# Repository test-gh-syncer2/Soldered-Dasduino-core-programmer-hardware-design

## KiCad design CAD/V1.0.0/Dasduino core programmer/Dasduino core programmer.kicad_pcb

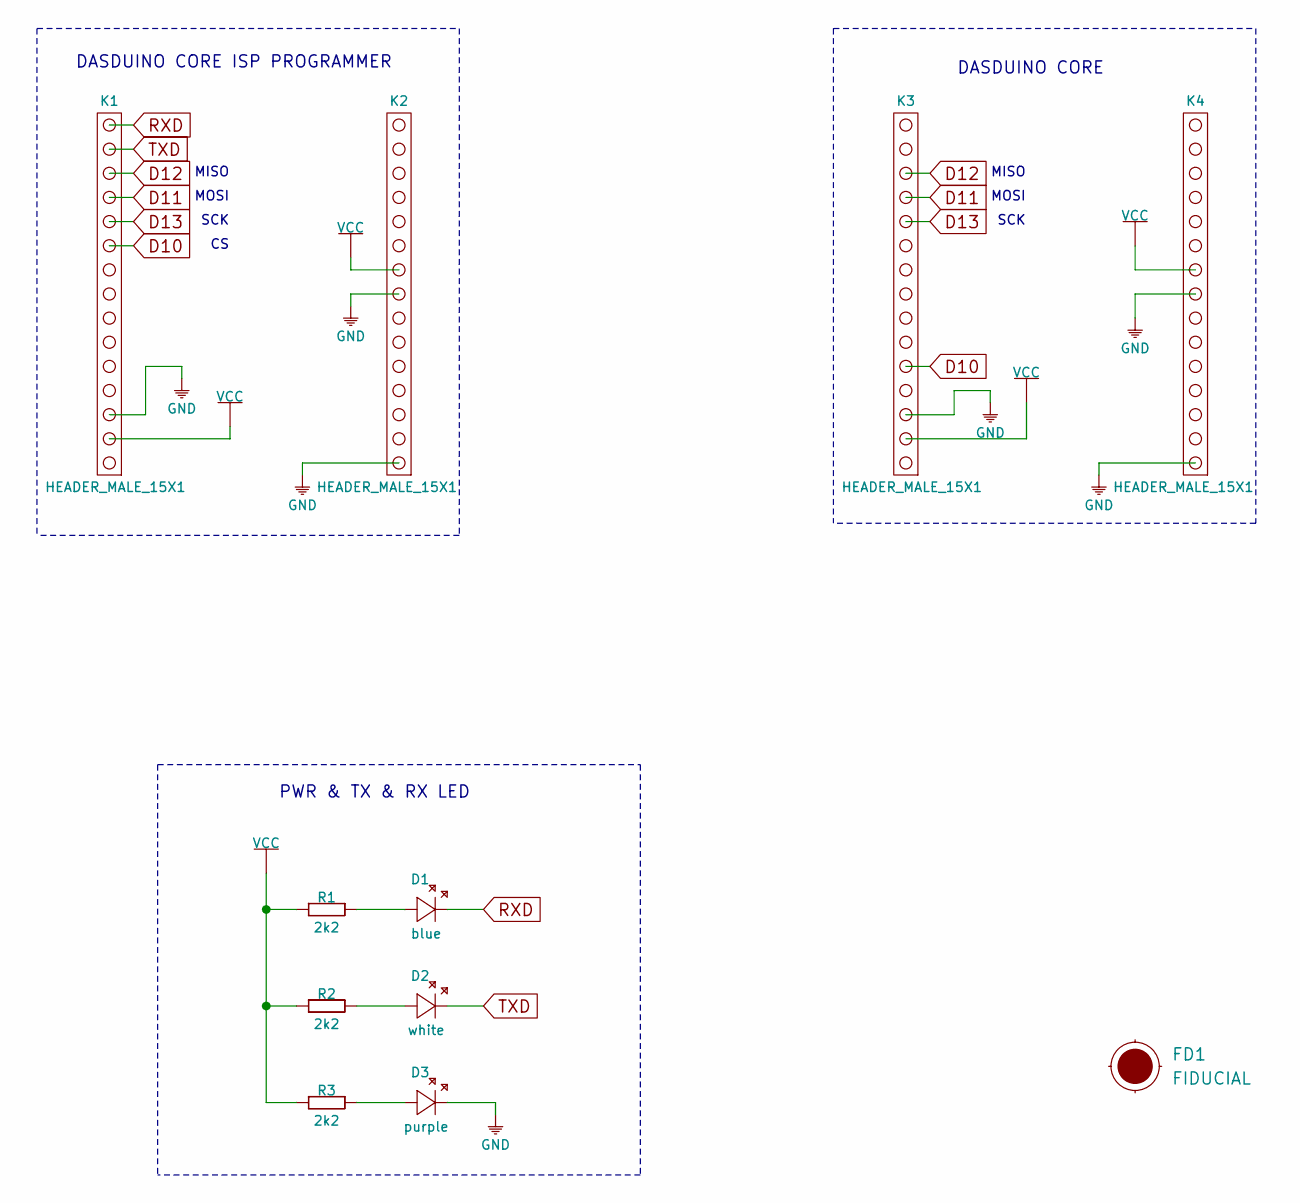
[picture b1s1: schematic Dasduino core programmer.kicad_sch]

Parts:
D1: blue; 0402LED
D2: white; 0402LED
D3: purple; 0402LED
FD1: FIDUCIAL; FIDUCIAL_23
K1, K2, K3, K4: HEADER_MALE_15X1
R1, R2, R3: 2k2; 0402R

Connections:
D10: K1.10, K3.5
D11: K1.12, K3.12
D12: K1.13, K3.13
D13: K1.11, K3.11
GND: D3.2 (K), K1.3, K2.1, K2.8, K3.3, K4.1, K4.8
unnamed: D1.1 (A), R1.2
unnamed: D2.1 (A), R2.2
unnamed: D3.1 (A), R3.2
RXD: D1.2 (K), K1.15
TXD: D2.2 (K), K1.14
VCC: K1.2, K2.9, K3.2, K4.9, R1.1, R2.1, R3.1

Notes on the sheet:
MISO
MOSI
SCK
PWR & TX & RX LED
DASDUINO CORE ISP PROGRAMMER
DASDUINO CORE

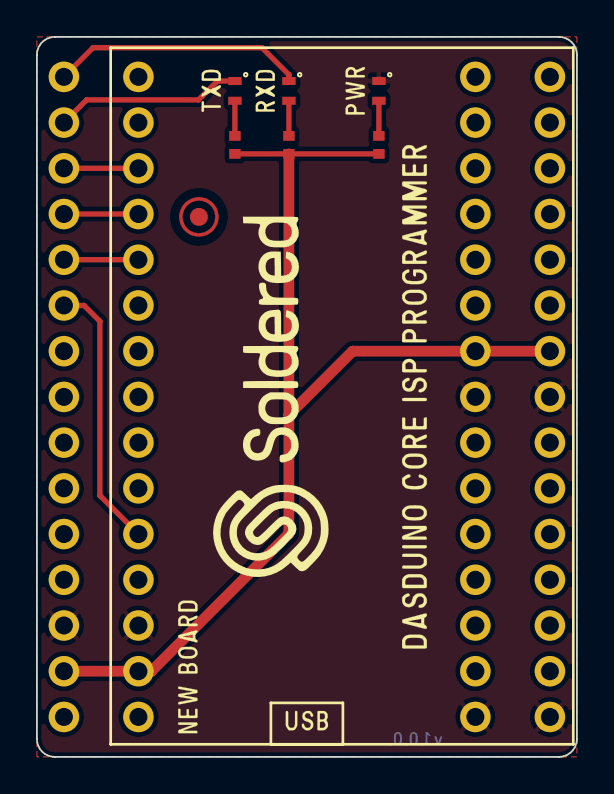
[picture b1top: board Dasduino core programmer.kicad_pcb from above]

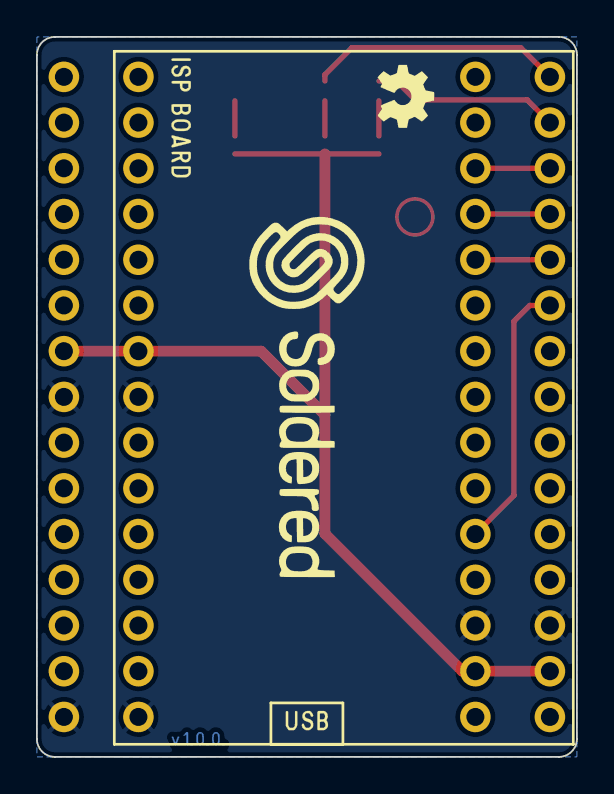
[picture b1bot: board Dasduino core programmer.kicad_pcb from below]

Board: 2 copper layers, 30.0 x 40.0 mm, 12 parts (3 on the bottom side), 11 nets.

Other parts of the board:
Ref**: Val**; Version1.0.0.

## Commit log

2021-09-23 Syncing to git
2021-09-23 Updating open source files.
